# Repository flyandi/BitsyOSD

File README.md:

BitsyOSD
=======

BitsyOSD is a full featured standalone OSD firmware with a modern design for the MinimOSD Hardware. 

It was specifically created for Multirotors (FPV Racing), Aircrafts and Ground Vehicles.

Full video at 
http://www.youtube.com/watch?v=92WtLzoAQVY

## Why another OSD?

There are plenty of OSD options out there but I needed an OSD that was easy to maintain but still had all the features that I wanted. That's why I created BitsyOSD - a minimal configuration OSD that works right of the "box" (yes, there is a box that you can print on your 3D printer).

The OSD itself has a fixed layout that provides all essential information and only requires configuration of the GPS. 

BitsyOSD supports the standard NEMA GPS as well DJI's Naza protocol.

BitsyOSD also supports no GPS and displays GPS unrelated values - making BitsyOSD a all around solution.

## Features

Currently BitsyOSD implements the following values in a fixed layout that is configurable and can be easily adapted to your needs:

* Speed 
* Altitude (ASL, AGL)
* Heading (AGH, BGH)
* Simple Variometer
* Traveled Distance
* Home Heading Indicator 
* Home Distance
* Flight Timer
* GPS Statuses
* GPS Coordinates
* Battery 1 Voltage Monitoring
* Battery 2 Voltage Monitoring
* Low Battery Alerts
* RSSI (*)
* New in 1.4: No GPS Mode - enables a super minimal OSD mode

**Please be aware that BitsyOSD doesn't have any outside configuration possibilities and all setup needs to be done via the code base**

## Hardware Requirements

You need a MinimOSD (duh!) and a GPS. Currently BitsyOSD supports any NEMA compatible GPS and the DJI Naza GPS.

I highly recommend to get the Micro MinimOSD Hardware which contains better filtering and additional inputs for Battery monitoring in a very compact size.

Get them from ReadyToFlyQuads (http://www.readytoflyquads.com/micro-minimosd).

If you have a DJI Naza Controller, you can use an Y-Cable to split the cable from the Naza GPS and directly connect it to the MinimOSD.

## Get Started

You don't need to be an code expert but I assume that you have the following things ready to go:

* Arduino IDE installed on your computer
* NodeJS installed
* GIT installed
* MinimOSD hardware
* USB FTDI TTL serial adapter
* GPS Module and connection cable

Next you need to download this project. Navigate to a directory where you want to keep the BitsyOSD code and clone the project via git.

```shell
git clone https://github.com/FPVTools/BitsyOSD
````

A quick hint: Connect the MinimOSD to a TV if you want to see whats going on with your MinimOSD during the setup process.

### Install Libraries

BitsyOSD is using several libraries that need to be installed to your Arduino IDE. Copy and paste all of the libraries found in ```libraries/``` to your Arduino's IDE libraries folder and restart the Arduino IDE. 

Learn more how to install libraries in Arduino at [http://arduino.cc/en/Guide/Libraries]

### Upload the font

BitsyOSD is using a custom font that needs to be uploaded to the MinimOSD. The entire font upload process is outside of the main code base to keep the size small. 

**Note: You need to redo this process if the font set changes in future firmware updates**

Connect the MinimOSD via the USB FTDI TTL serial adapter to your computer and upload the file ```font/fontupload/fontupload.ino``` via the Arduino IDE to the MinimOSD. If you have a screen connected, you should be able to see the current font set on it.

Open a command console and navigate to the folder ```font/```. Execute the following command and follow the on-screen instructions.

```shell
node uploadfont.js
```

This process may take some time and you should see the new font set on your display if you have a screen connected.

### Upload the firmware

Make sure the MinimOSD is connected to your computer via the USB FTDI TTL serial adapter. Open the file ```BitsyOSD/BitsyOSD.ino``` and click ```Upload``` in the Arduino IDE.

If you installed the libraries as well uploaded the font correctly, you now have a working MinimOSD with BitsyOSD. 

## Breakout Board

This project also includes the break-out board schematics for Eagle. The break-out board follows the standard flight controller size of 32x32mm and routes all necessary hook up points to one header.

Go to the board directory to learn more.

## License

Copyright (c) 2017.  All rights reserved.

This program is free software: you can redistribute it and/or modify
it under the terms of the GNU General Public License as published by
the Free Software Foundation, either version 3 of the License, or
(at your option) any later version.

This program is distributed in the hope that it will be useful,
but WITHOUT ANY WARRANTY; without even the implied warranty of
MERCHANTABILITY or FITNESS FOR A PARTICULAR PURPOSE. See the
GNU General Public License for more details.

You should have received a copy of the GNU General Public License
along with this program. If not, see <http://www.gnu.org/licenses/>

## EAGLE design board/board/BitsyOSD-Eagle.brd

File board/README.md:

BitsyOSD Breakout Board
=======

This directory contains the breakout board for the Micro MinimOSD Hardware.

It routes all necessary hookup points to a single header. Included are the schematics, board and CNC GCode files.

## License

Copyright (c) 2017.  All rights reserved.

This program is free software: you can redistribute it and/or modify
it under the terms of the GNU General Public License as published by
the Free Software Foundation, either version 3 of the License, or
(at your option) any later version.

This program is distributed in the hope that it will be useful,
but WITHOUT ANY WARRANTY; without even the implied warranty of
MERCHANTABILITY or FITNESS FOR A PARTICULAR PURPOSE. See the
GNU General Public License for more details.

You should have received a copy of the GNU General Public License
along with this program. If not, see <http://www.gnu.org/licenses/>

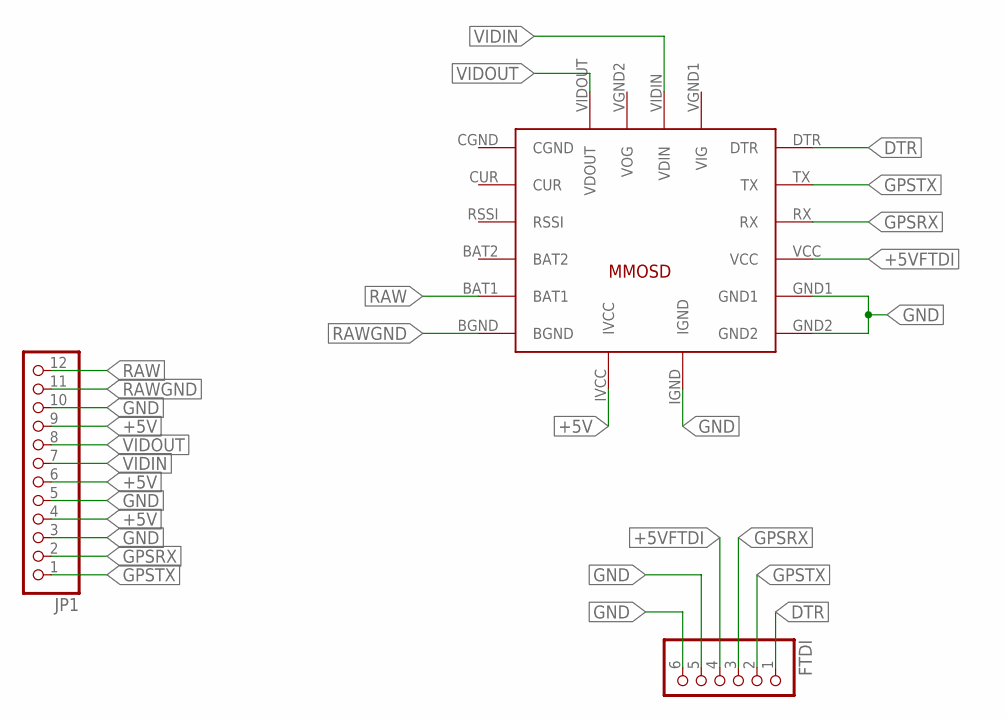
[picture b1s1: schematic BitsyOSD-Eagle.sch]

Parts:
FTDI: PINHD-1X6; 1X06
JP1: PINHD-1X12; 1X12
U$2: MICROMINIMOSDPWR; MMOSDNVDVID

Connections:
+5V: JP1.4, JP1.6, JP1.9, U$2.IVCC
+5VFTDI: FTDI.4, U$2.VCC
BAT2: U$2.BAT2
CGND: U$2.CGND
DTR: FTDI.1, U$2.DTR
GND: FTDI.5, FTDI.6, JP1.3, JP1.5, JP1.10, U$2.GND1, U$2.GND2, U$2.IGND
GPSRX: FTDI.3, JP1.2, U$2.RX
GPSTX: FTDI.2, JP1.1, U$2.TX
RAW: JP1.12, U$2.BAT1
RAWGND: JP1.11, U$2.BGND
VIDIN: JP1.7, U$2.VIDIN (VDIN)
VIDOUT: JP1.8, U$2.VIDOUT (VDOUT)

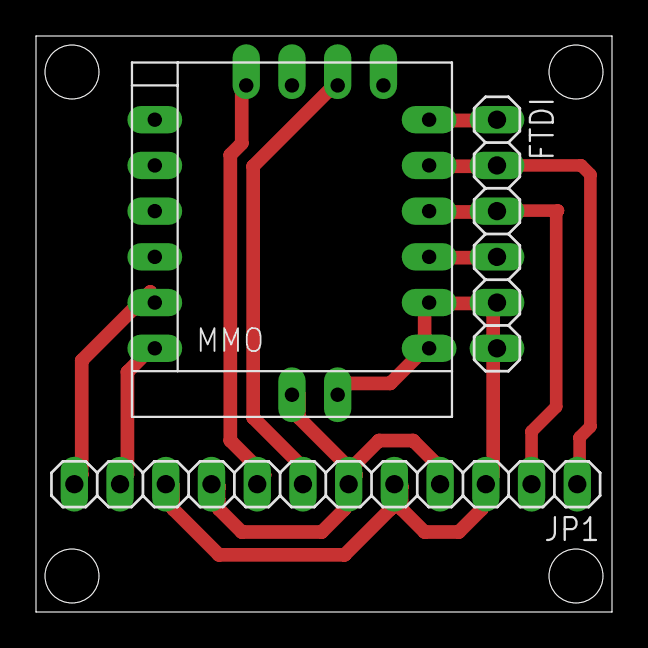
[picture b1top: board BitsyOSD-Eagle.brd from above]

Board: 2 copper layers, 32.0 x 32.0 mm, 3 parts (0 on the bottom side), 10 nets.

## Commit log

2015-04-09 Initial
2015-04-09 Cleanup
2015-04-09 Added GiF Animation
2015-04-24 Fixed GCC compiler errors and updated FastSerial lib to be standalone (without AP_ headers)
2015-04-24 Added Heartbeat for new Hardware
2015-04-24 Added 3d printed box for Micro Hardware
2015-08-04 Added Voltage and RSSI processing
2015-08-04 Implemented voltage display
2015-08-04 Added percentage display for battery
2015-08-05 Added low voltage warning
2015-08-05 Updating docs
2015-08-31 Changing NEMA parser boot sequence
2015-09-02 Rewired the inclusion of constants, configs and default values
2015-09-02 Updated 1.2.0 release docs
2016-08-22 Fixed font uploader and updated to use npm modules
2016-08-30 Updated Information
2016-09-19 Release 1.4 - Added No GPS Mode
2016-09-20 Version change
2017-07-20 Adds breakout board
2017-07-20 Updates readme
2021-11-20 Fixes to the fontupload tool
